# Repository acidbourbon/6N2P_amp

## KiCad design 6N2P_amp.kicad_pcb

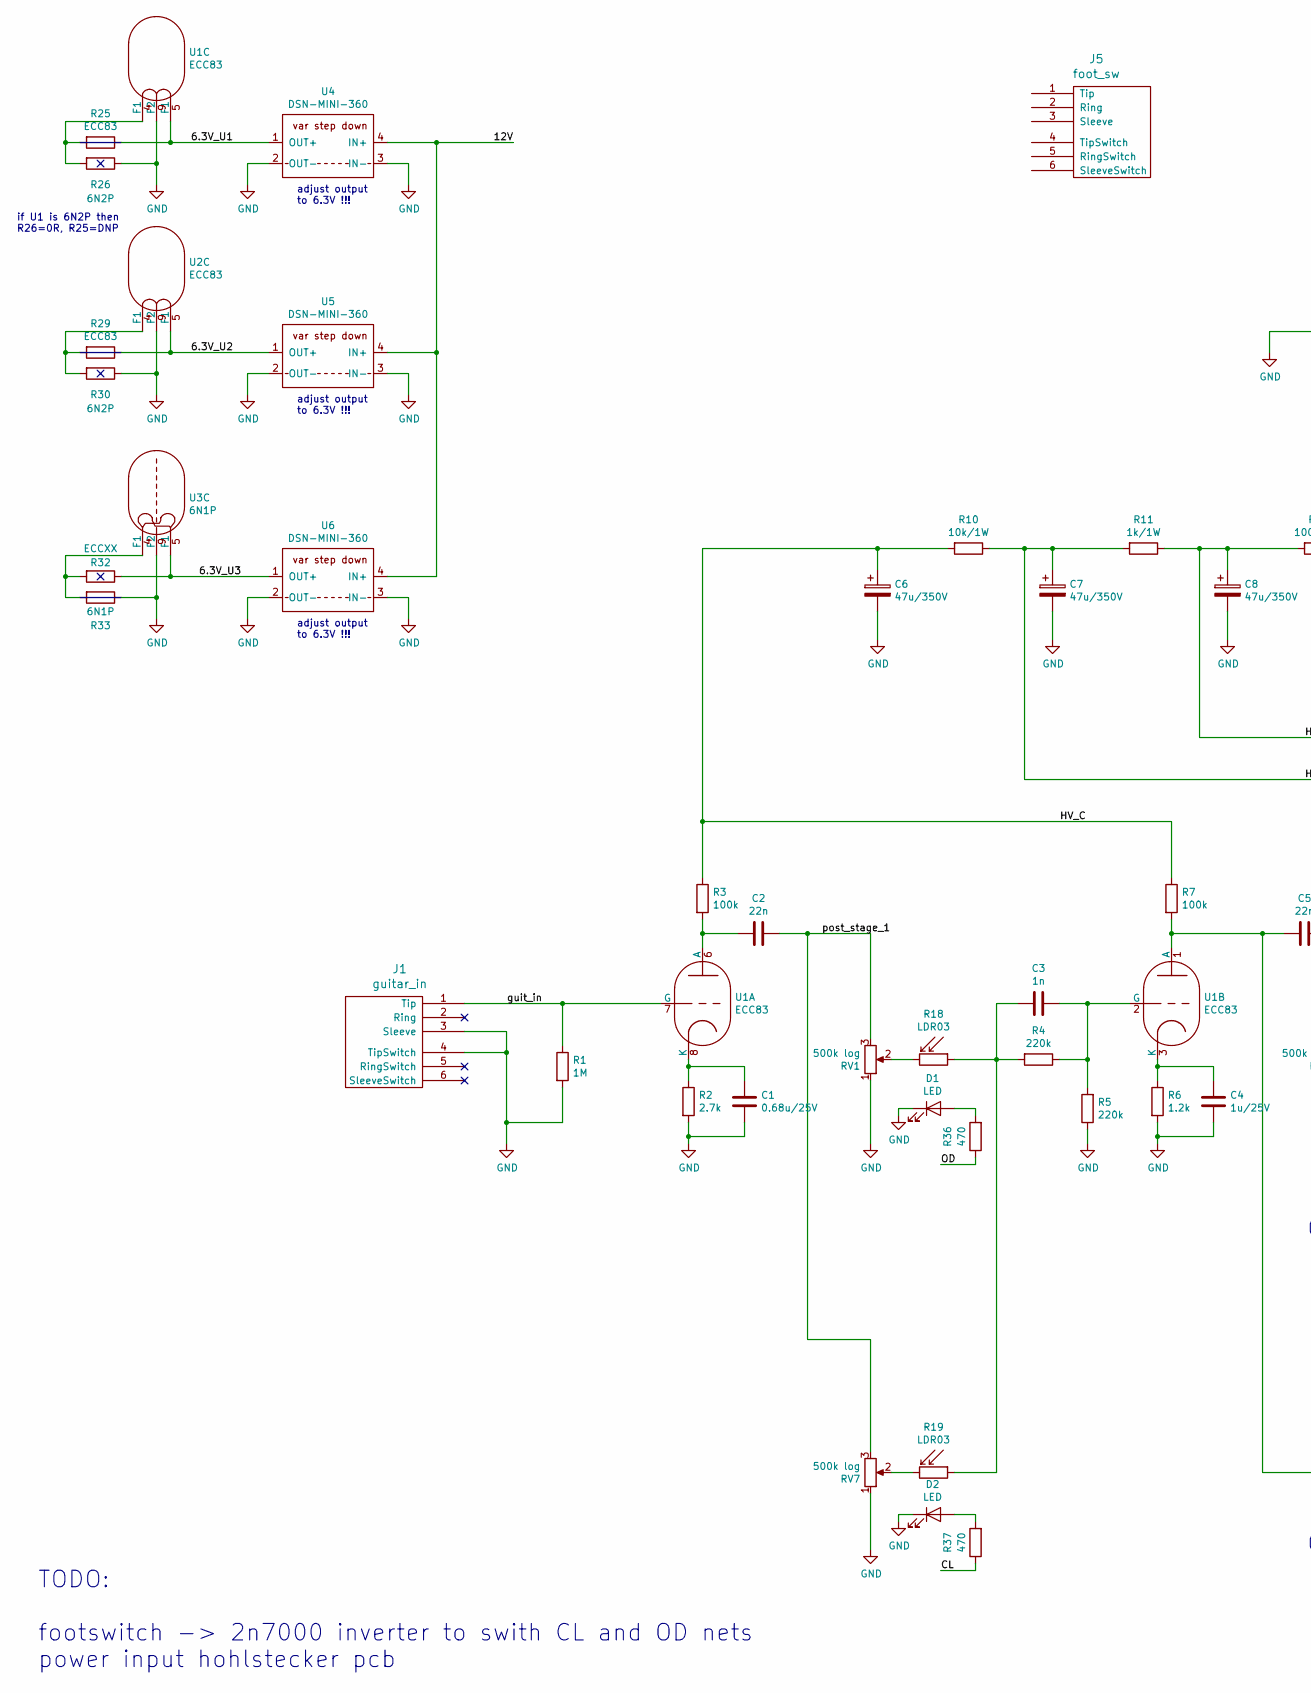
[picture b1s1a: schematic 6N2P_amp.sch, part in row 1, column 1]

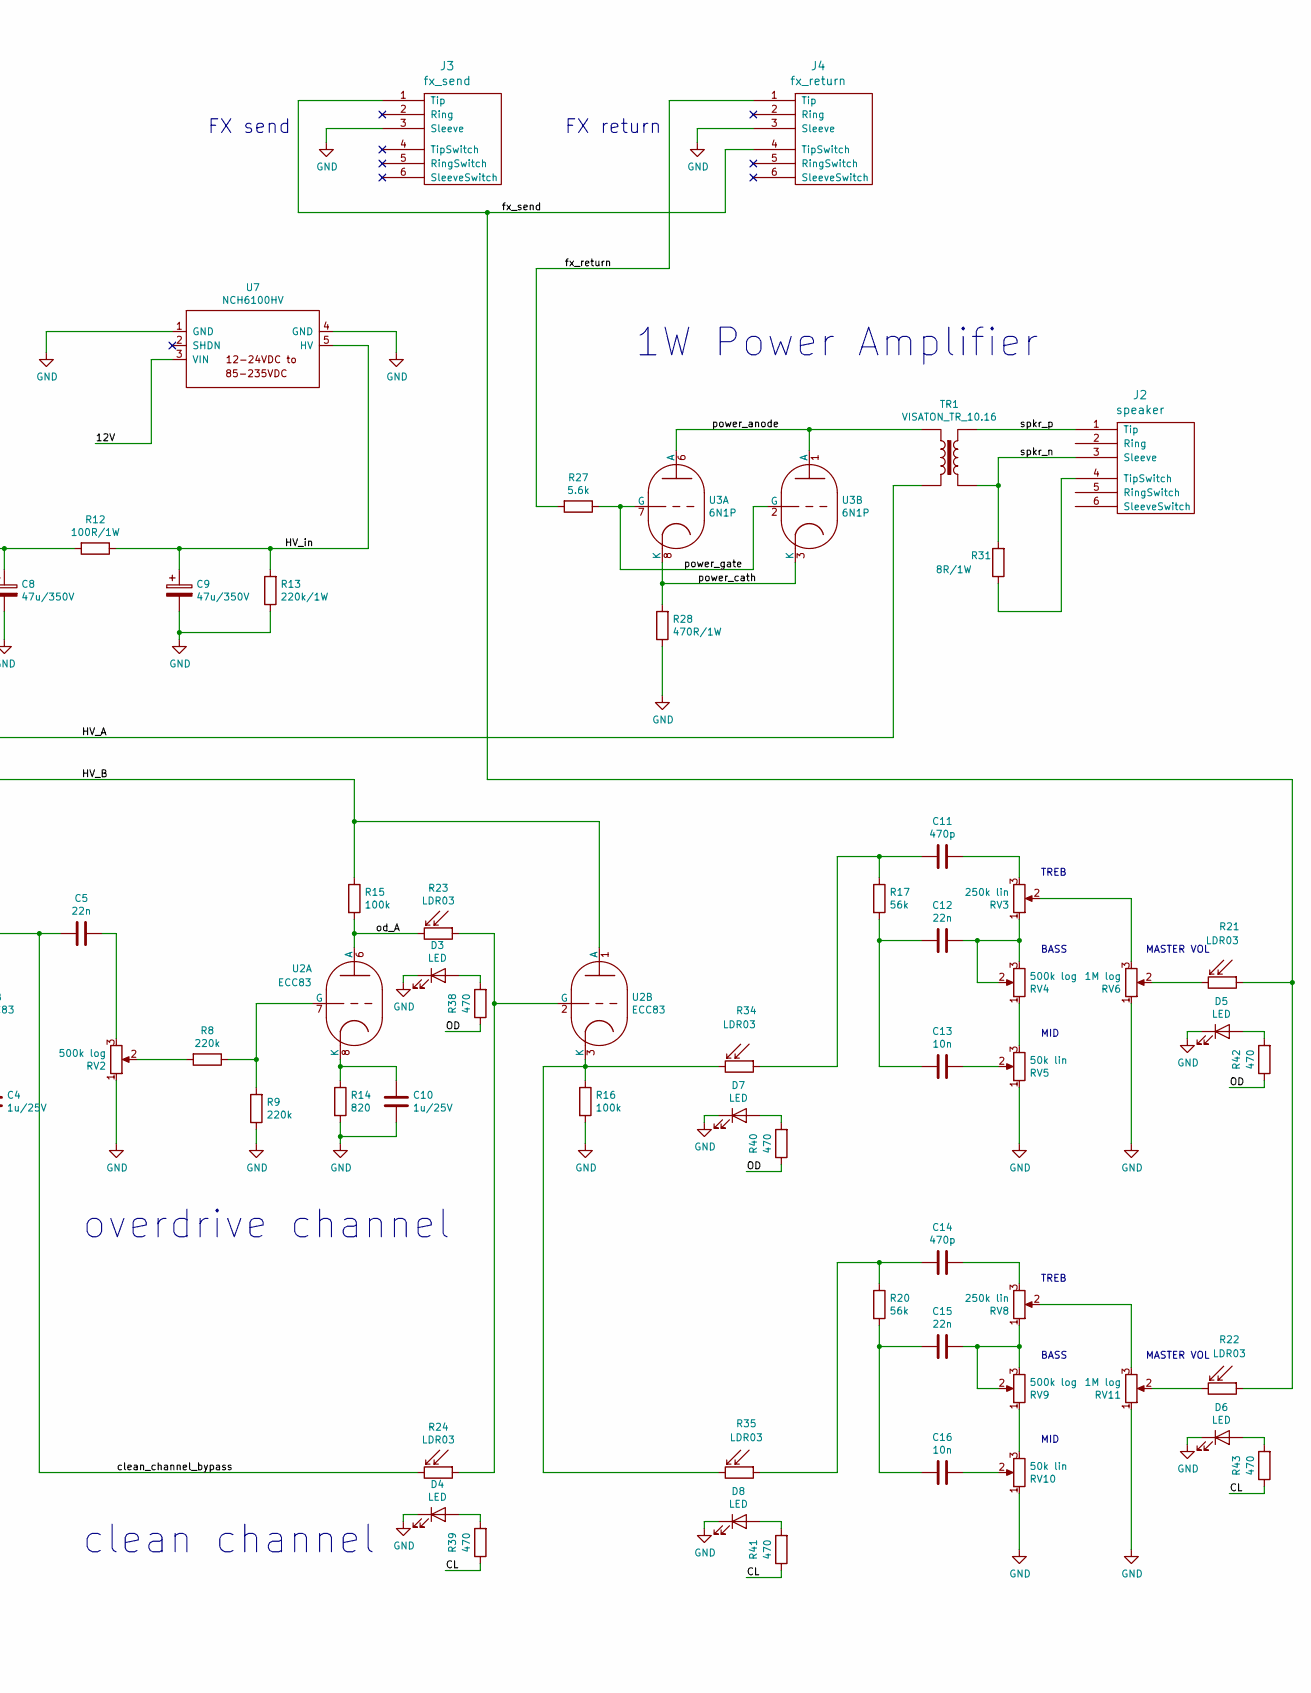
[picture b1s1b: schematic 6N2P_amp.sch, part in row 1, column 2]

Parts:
C1: 0.68u/25V; C_Rect_L9.0mm_W4.0mm_P7.50mm_MKT
C2, C5, C12, C15: 22n; C_Rect_L9.0mm_W4.0mm_P7.50mm_MKT
C3: 1n; C_Rect_L9.0mm_W4.0mm_P7.50mm_MKT
C4, C10: 1u/25V; C_Rect_L9.0mm_W4.0mm_P7.50mm_MKT
C6, C7, C8, C9: 47u/350V; CP_Radial_D16.0mm_P7.50mm
C11, C14: 470p; C_Rect_L9.0mm_W4.0mm_P7.50mm_MKT
C13, C16: 10n; C_Rect_L9.0mm_W4.0mm_P7.50mm_MKT
D1, D2, D3, D4, D5, D6, D7, D8: LED; LED_D5.0mm
J1: guitar_in; Reichelt_EBS63P
J2: speaker; Reichelt_EBS63P
J3: fx_send; Reichelt_EBS63P
J4: fx_return; Reichelt_EBS63P
J5: foot_sw; Reichelt_EBS63P
R1: 1M; R_Axial_DIN0207_L6.3mm_D2.5mm_P10.16mm_Horizontal
R2: 2.7k; R_Axial_DIN0207_L6.3mm_D2.5mm_P10.16mm_Horizontal
R3, R7, R15, R16: 100k; R_Axial_DIN0207_L6.3mm_D2.5mm_P10.16mm_Horizontal
R4, R5, R8, R9: 220k; R_Axial_DIN0207_L6.3mm_D2.5mm_P10.16mm_Horizontal
R6: 1.2k; R_Axial_DIN0207_L6.3mm_D2.5mm_P10.16mm_Horizontal
R10: 10k/1W; R_Axial_DIN0207_L6.3mm_D2.5mm_P10.16mm_Horizontal
R11: 1k/1W; R_Axial_DIN0207_L6.3mm_D2.5mm_P10.16mm_Horizontal
R12: 100R/1W; R_Axial_DIN0207_L6.3mm_D2.5mm_P10.16mm_Horizontal
R13: 220k/1W; R_Axial_DIN0207_L6.3mm_D2.5mm_P10.16mm_Horizontal
R14: 820; R_Axial_DIN0207_L6.3mm_D2.5mm_P10.16mm_Horizontal
R17, R20: 56k; R_Axial_DIN0207_L6.3mm_D2.5mm_P10.16mm_Horizontal
R18, R19, R21, R22, R23, R24, R34, R35: LDR03; R_LDR_4.9x4.2mm_P2.54mm_Vertical
R25, R29: ECC83; R_Axial_DIN0204_L3.6mm_D1.6mm_P2.54mm_Vertical
R26, R30: 6N2P; R_Axial_DIN0204_L3.6mm_D1.6mm_P2.54mm_Vertical
R27: 5.6k; R_Axial_DIN0207_L6.3mm_D2.5mm_P10.16mm_Horizontal
R28: 470R/1W; R_Axial_DIN0207_L6.3mm_D2.5mm_P10.16mm_Horizontal
R31: 8R/1W; R_Axial_DIN0207_L6.3mm_D2.5mm_P10.16mm_Horizontal
R32: ECCXX; R_Axial_DIN0204_L3.6mm_D1.6mm_P2.54mm_Vertical
R33: 6N1P; R_Axial_DIN0204_L3.6mm_D1.6mm_P2.54mm_Vertical
R36, R37, R38, R39, R40, R41, R42, R43: 470; R_Axial_DIN0309_L9.0mm_D3.2mm_P2.54mm_Vertical
RV1, RV2, RV4: 500k log; PinHeader_1x03_P2.54mm_Vertical
RV3: 250k lin; PinHeader_1x03_P2.54mm_Vertical
RV5: 50k lin; PinHeader_1x03_P2.54mm_Vertical
RV6: 1M log; PinHeader_1x03_P2.54mm_Vertical
RV7, RV9: 500k log; Potentiometer_Alps_RK163_Single_Horizontal
RV8: 250k lin; Potentiometer_Alps_RK163_Single_Horizontal
RV10: 50k lin; Potentiometer_Alps_RK163_Single_Horizontal
RV11: 1M log; Potentiometer_Alps_RK163_Single_Horizontal
TR1: VISATON_TR_10.16
U1, U2: ECC83; tube_gzc9-b
U3: 6N1P; socket_gzc9-b
U4, U5, U6: DSN-MINI-360
U7: NCH6100HV

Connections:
/6.3V_U1: R25.1, U1.5 (F1), U4.1 (OUT+)
/6.3V_U2: R29.1, U2.5 (F1), U5.1 (OUT+)
/6.3V_U3: R32.1, U3.5 (F1), U6.1 (OUT+)
/12V: U4.4 (IN+), U5.4 (IN+), U6.4 (IN+), U7.3 (VIN)
/CL: R37.1, R39.1, R41.1, R43.1
/HV_A: C8.1, R11.1, R12.2, TR1.2
/HV_B: C7.1, R10.1, R11.2, R15.1, U2.1 (A)
/HV_C: C6.1, R3.1, R7.1, R10.2
/HV_in: C9.1, R12.1, R13.2, U7.5 (HV)
/OD: R36.1, R38.1, R40.1, R42.1
/clean_channel_bypass: C5.2, R7.2, R24.2, U1.1 (A)
/fx_return: J4.1 (Tip), R27.2
/fx_send: J3.1 (Tip), J4.4 (TipSwitch), R21.1, R22.1
/guit_in: J1.1 (Tip), R1.1, U1.7 (G)
/od_A: R15.2, R23.2, U2.6 (A)
/post_stage_1: C2.1, RV1.3, RV7.3
/power_anode: TR1.1, U3.1 (A), U3.6 (A)
/power_cath: R28.2, U3.3 (K), U3.8 (K)
/power_gate: R27.1, U3.2 (G), U3.7 (G)
/spkr_n: J2.3 (Sleeve), R31.2, TR1.3
/spkr_p: J2.1 (Tip), TR1.4
GND: C1.2, C4.2, C6.2, C7.2, C8.2, C9.2, C10.2, D1.1 (K), D2.1 (K), D3.1 (K), D4.1 (K), D5.1 (K), D6.1 (K), D7.1 (K), D8.1 (K), J1.3 (Sleeve), J1.4 (TipSwitch), J3.3 (Sleeve), J4.3 (Sleeve), R1.2, R2.2, R5.1, R6.2, R9.1, R13.1, R14.2, R16.2, R26.1, R28.1, R30.1, R33.1, RV1.1, RV2.1, RV5.1, RV6.1, RV7.1, RV10.1, RV11.1, U1.9 (F2), U2.9 (F2), U3.9 (F2), U4.2 (OUT-), U4.3 (IN-), U5.2 (OUT-), U5.3 (IN-), U6.2 (OUT-), U6.3 (IN-), U7.1 (GND), U7.4 (GND)
unnamed: C1.1, R2.1, U1.8 (K)
unnamed: C2.2, R3.2, U1.6 (A)
unnamed: C3.1, R4.1, R5.2, U1.2 (G)
unnamed: C3.2, R4.2, R18.1, R19.1
unnamed: C4.1, R6.1, U1.3 (K)
unnamed: C5.1, RV2.3
unnamed: C10.1, R14.1, U2.8 (K)
unnamed: C11.1, RV3.3
unnamed: C11.2, R17.1, R34.1
unnamed: C12.1, RV3.1, RV4.2, RV4.3
unnamed: C12.2, C13.2, R17.2
unnamed: C13.1, RV5.2
unnamed: C14.1, RV8.3
unnamed: C14.2, R20.1, R35.1
unnamed: C15.1, RV8.1, RV9.2, RV9.3
unnamed: C15.2, C16.2, R20.2
unnamed: C16.1, RV10.2
unnamed: D1.2 (A), R36.2
unnamed: D2.2 (A), R37.2
unnamed: D3.2 (A), R38.2
unnamed: D4.2 (A), R39.2
unnamed: D5.2 (A), R42.2
unnamed: D6.2 (A), R43.2
unnamed: D7.2 (A), R40.2
unnamed: D8.2 (A), R41.2
unnamed: J2.4 (TipSwitch), R31.1
unnamed: R8.1, R9.2, U2.7 (G)
unnamed: R8.2, RV2.2
unnamed: R16.1, R34.2, R35.2, U2.3 (K)
unnamed: R18.2, RV1.2
unnamed: R19.2, RV7.2
unnamed: R21.2, RV6.2
unnamed: R22.2, RV11.2
unnamed: R23.1, R24.1, U2.2 (G)
unnamed: R25.2, R26.2, U1.4 (F1)
unnamed: R29.2, R30.2, U2.4 (F1)
unnamed: R32.2, R33.2, U3.4 (F1)
unnamed: RV3.2, RV6.3
unnamed: RV4.1, RV5.3
unnamed: RV9.1, RV10.3
unnamed: RV8.2, RV11.3

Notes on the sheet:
TREB
BASS
MID
MASTER VOL
clean channel
overdrive channel
if U1 is 6N2P then R26=0R, R25=DNP
1W Power Amplifier
FX send
FX return
adjust output to 6.3V !!!
TODO: footswitch -> 2n7000 inverter to swith CL and OD nets power input hohlstecker pcb

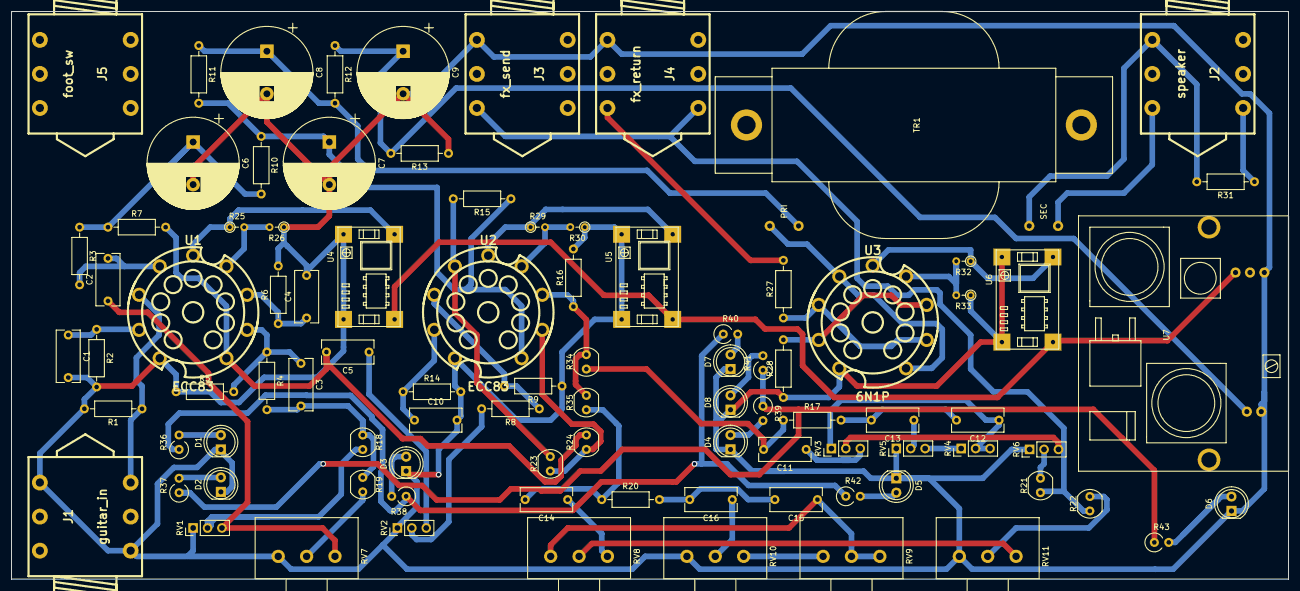
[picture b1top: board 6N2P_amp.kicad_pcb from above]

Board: 2 copper layers, 225.0 x 100.0 mm, 91 parts (0 on the bottom side), 63 nets.

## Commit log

2020-04-19 snap
2020-04-19 it is making progress
2020-04-26 some progress ... made symbols for dc dc converters and transformer
2020-08-24 snap, ... started experimental routing
2020-08-24 help text in layout
2020-08-24 added the ldr leds
2020-08-24 introduced foot switch jack
2020-08-24 genug fuer heute
2020-08-25 more LDRs
2020-08-25 LDRs
2020-08-25 more routing
2020-08-26 new evening
2020-08-26 we have resistors now for the LEDs
2020-08-26 resistors and spacings
2020-08-26 everything routed. woah!
2021-04-18 pdf of schematic
